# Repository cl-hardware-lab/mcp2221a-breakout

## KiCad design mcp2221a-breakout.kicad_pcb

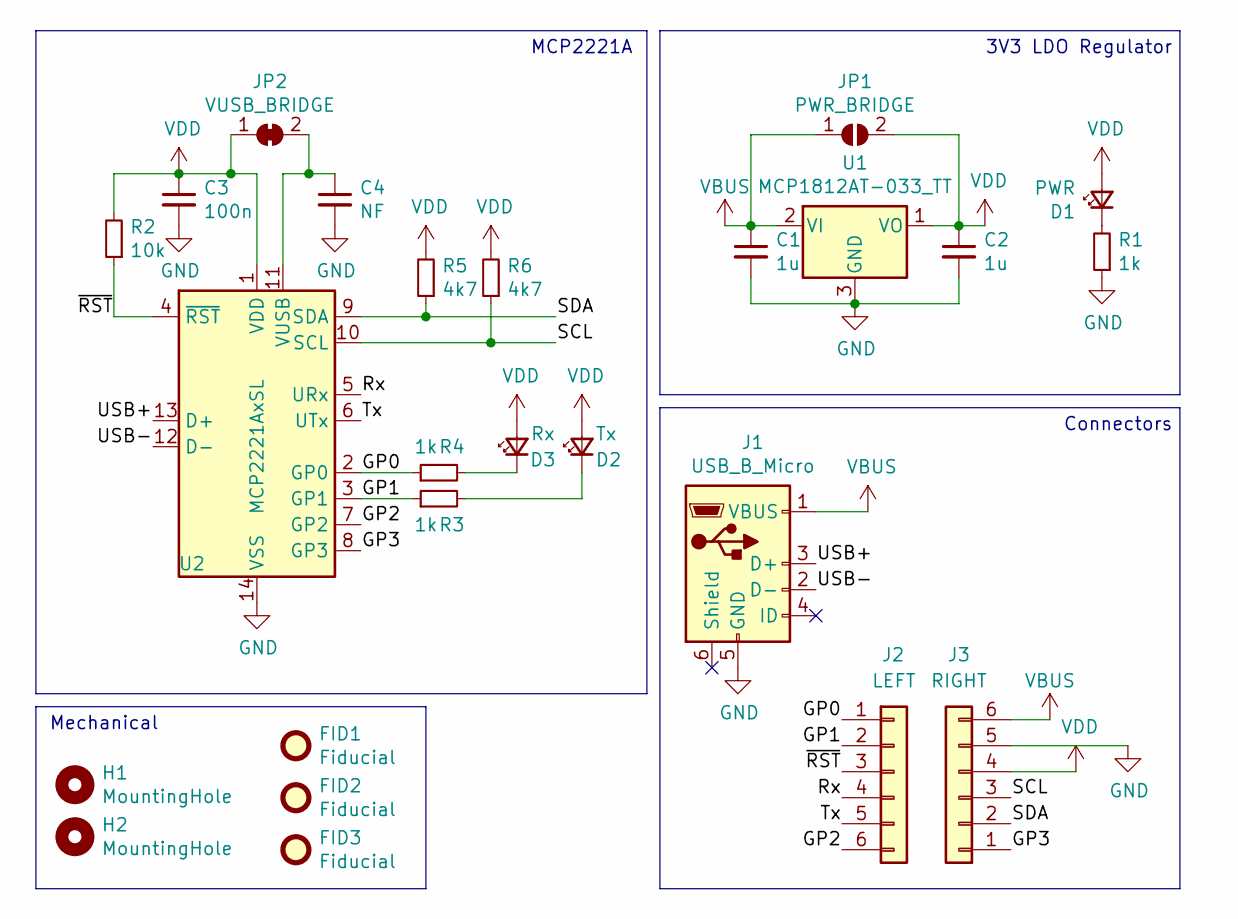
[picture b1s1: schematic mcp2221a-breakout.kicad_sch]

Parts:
C1, C2: 1u; C_0603_1608Metric
C3: 100n; C_0603_1608Metric
C4: NF; C_0603_1608Metric
D1: PWR; LED_0805_2012Metric
D2: Tx; LED_0805_2012Metric
D3: Rx; LED_0805_2012Metric
FID1, FID2, FID3: Fiducial; Fiducial_1mm_Mask2mm
H1, H2: MountingHole; MountingHole_2.7mm_M2.5_DIN965_Pad
J1: USB_B_Micro; USB_Micro-B_Molex-105017-0001
J2: LEFT; PinHeader_1x06_P2.54mm_Vertical
J3: RIGHT; PinHeader_1x06_P2.54mm_Vertical
JP1: PWR_BRIDGE; SolderJumper-2_P1.3mm_Open_RoundedPad1.0x1.5mm
JP2: VUSB_BRIDGE; SolderJumper-2_P1.3mm_Bridged_RoundedPad1.0x1.5mm
R1, R3, R4: 1k; R_0603_1608Metric
R2: 10k; R_0603_1608Metric
R5, R6: 4k7; R_0603_1608Metric
U1: MCP1812AT-033_TT; SOT-23
U2: MCP2221AxSL; SOIC-14_3.9x8.7mm_P1.27mm

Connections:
/GP0: J2.1, R4.1, U2.2 (GP0)
/GP1: J2.2, R3.1, U2.3 (GP1)
/GP2: J2.6, U2.7 (GP2)
/GP3: J3.1, U2.8 (GP3)
/Rx: J2.4, U2.5 (URx)
/SCL: J3.3, R6.1, U2.10 (SCL)
/SDA: J3.2, R5.1, U2.9 (SDA)
/Tx: J2.5, U2.6 (UTx)
/USB+: J1.3 (D+), U2.13 (D+)
/USB-: J1.2 (D-), U2.12 (D-)
/~RST: J2.3, R2.1, U2.4 (~RST)
GND: C1.2, C2.2, C3.2, C4.2, J1.5 (GND), J3.5, R1.1, U1.3 (GND), U2.14 (VSS)
unnamed: C4.1, JP2.2 (B), U2.11 (VUSB)
unnamed: D1.1 (K), R1.2
unnamed: D2.1 (K), R3.2
unnamed: D3.1 (K), R4.2
VBUS: C1.1, J1.1 (VBUS), J3.6, JP1.1 (A), U1.2 (VI)
VDD: C2.1, C3.1, D1.2 (A), D2.2 (A), D3.2 (A), J3.4, JP1.2 (B), JP2.1 (A), R2.2, R5.2, R6.2, U1.1 (VO), U2.1 (VDD)

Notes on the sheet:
3V3 LDO Regulator
Connectors
Mechanical
MCP2221A

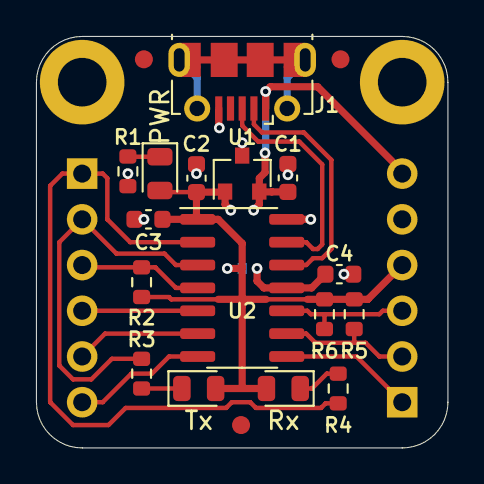
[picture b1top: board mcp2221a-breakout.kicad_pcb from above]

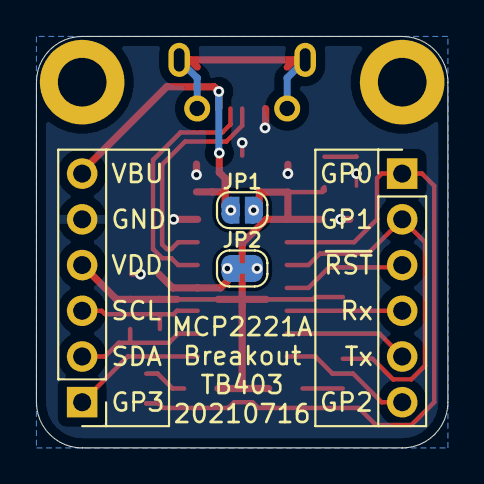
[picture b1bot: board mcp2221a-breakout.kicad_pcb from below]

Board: 2 copper layers, 22.9 x 22.9 mm, 25 parts (4 on the bottom side), 18 nets.

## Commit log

2021-07-16 Initial Project Files
2021-07-16 Various Tweaks
    * Tidied up the schematic
    * Added I2C pullup resistors
    * Changed labels on LED1 & LED2 to Rx & Tx
2021-07-17 Tidy schematic a bit more
2021-07-17 Shrink board outline more
2021-07-19 Switch regulator
2022-03-28 Gerbers
2022-03-28 Panelization test
2022-03-28 Add ibom
